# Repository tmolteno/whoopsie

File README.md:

# whoopsie
A small open-source flying 18650 quadcopter.

## Required Components

* [Flywoo Robo 1202.5 11500kv motors](https://flywoo.net/products/flywoo-robo-rb1202-5-5500kv-11500kv-1-5mm-shaft-fpv-motor)
* [Happymodel ELRS all-in-one flight controller](http://www.happymodel.cn/index.php/2021/05/19/happymodel-elrs-f4-2g4-aio-5in1-flight-controller-built-in-spi-2-4ghz-elrs-rx/)
* Caddx ant (or similar)
* PCB and 3D printed frame

## Directories

* `/pcb/` contains the KiCAD layout, with the custom library for the motors and AIO board
* `/frame/` contains the FreeCAD file.

## TODO in v2 

* Modify the 3D printed frame to sit below the PCB, with the battery inset into the frame
* Update the camera mount
* Add a self-powered/charging buzzer to the PCB
* (?) Board-mounted RX if we go for a longer one 

## Gallery

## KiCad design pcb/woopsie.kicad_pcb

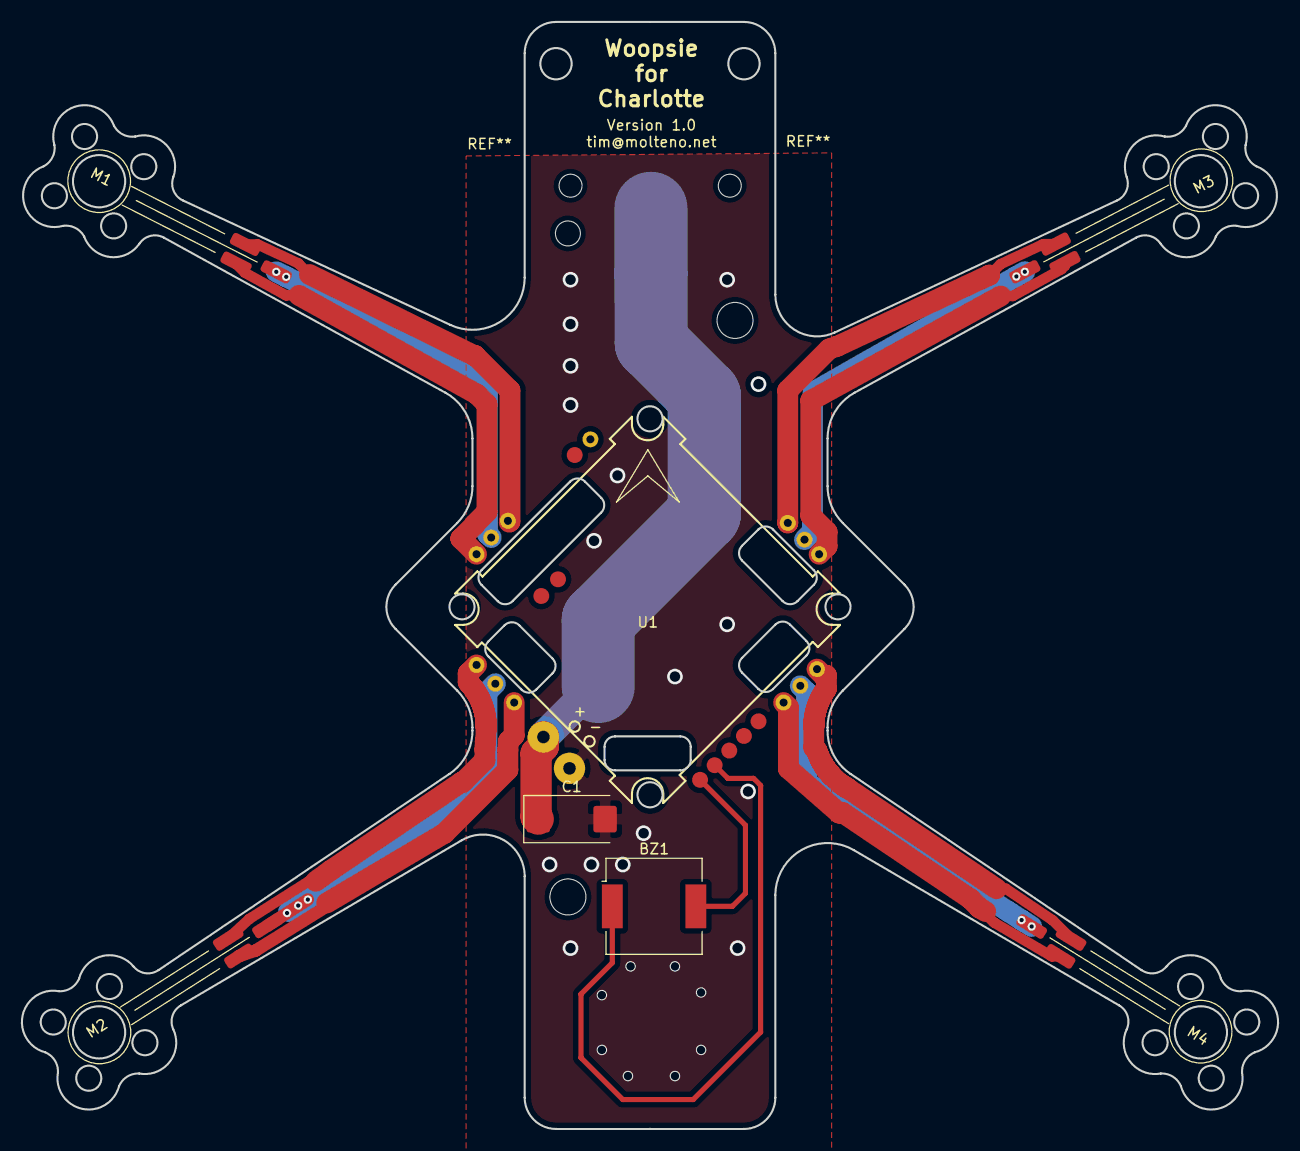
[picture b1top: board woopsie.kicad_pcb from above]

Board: 2 copper layers, 120.3 x 106.0 mm, 8 parts (1 on the bottom side), 16 nets.

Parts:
BT1: Battery_Cell; BatteryHolder_Keystone_1042_1x18650
BZ1: Buzzer; Buzzer_CUI_CPT-9019S-SMT
C1: CP; CP_EIA-7343-15_Kemet-W_Pad2.25x2.55mm_HandSolder
M1, M2, M3, M4: RB1202.5
U1: AIO_ELRS24; ELRS_24

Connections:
+BATT: BT1.1, C1.1, U1.11
GND: BT1.2, C1.2, U1.12
unnamed: BZ1.1, U1.14
unnamed: BZ1.2, U1.13
unnamed: M1.1, U1.5
unnamed: M1.2, U1.6
unnamed: M1.3, U1.7
unnamed: M2.1, U1.8
unnamed: M2.2, U1.9
unnamed: M2.3, U1.10
unnamed: M3.1, U1.21
unnamed: M3.2, U1.22
unnamed: M3.3, U1.23
unnamed: M4.1, U1.18
unnamed: M4.2, U1.19
unnamed: M4.3, U1.20

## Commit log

2021-08-27 Minor list of bits
2021-08-28 Added pictures and organised things a bit
2021-09-11 First version of the 1.1 camera mount. Rename file too
2021-09-22 Added STL files to simplify printing
